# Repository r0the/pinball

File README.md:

# Ausgabemodule für Flipperautomaten

Für das Fakultativfach *Technisches Konstruieren* am [Gymnasium Kirchenfeld](https://www.gymkirchenfeld.ch/), in welchem Schülerinnen und Schüler einen Flipperautomaten bauen, entwickle ich elektronische Anzeigemodule. Kern der Module bildet ein
[Arduino](https://www.arduino.cc/)-Mikrocontroller-Board.

## Funktionalität

Die Module bieten die folgende Funktionalität:

- Zählen der Punkte
- Anzeige des aktuellen Punktestands
- Abspielen von Audiodateien
- Speichern des Punktehöchststands (Highscore)
- Steuerung von Lampen oder Leuchtdioden des Automaten
- Anzeige eines Lauftextes (nur Modul B)

## Varianten

Es gibt zwei Varianten, welche sich in der Art des Displays unterscheiden.

- Das **Variante A** verwendet zur Anzeige des Punktestands fünf LED-Segmentanzeigen.
- Das **Variante B** stellt Punktestand und allenfalls weitere Informationen auf einer oder mehreren
  LED-Matrixanzeigen dar.

Zur Zeit steht pro Jahrgang steht nur eine Variante zu Verfügung.

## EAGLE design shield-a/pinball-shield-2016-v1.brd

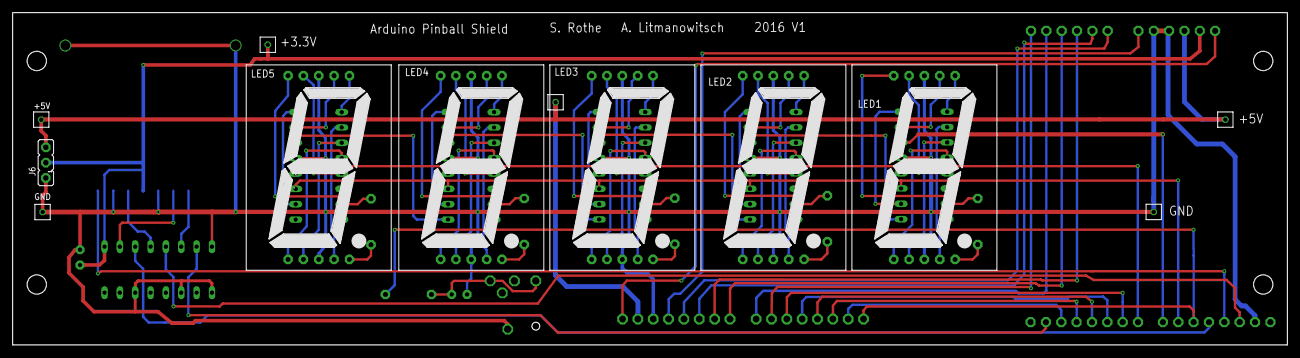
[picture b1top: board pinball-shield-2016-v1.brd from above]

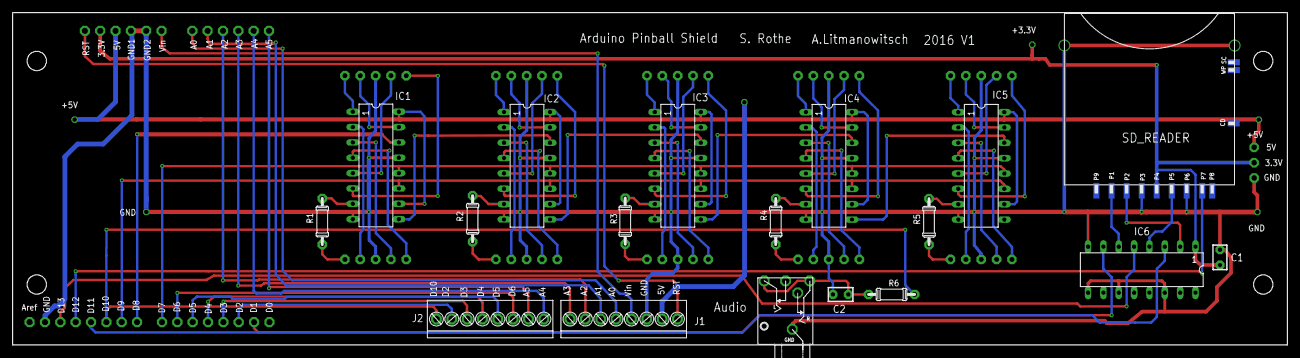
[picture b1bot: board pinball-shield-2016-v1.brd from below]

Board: 2 copper layers, 211.0 x 55.0 mm, 58 parts (18 on the bottom side), 77 nets.

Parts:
C1: 0.1uF; 02P101QK
C2: 1nF; 02P101QK
E$1: JACK_CONRAD_730294
E$2, E$3, E$4, E$5, E$8, E$9, E$10, E$12, E$13, E$14, E$15, E$16, E$17, E$18, E$19, E$20, E$21, E$22, E$23, E$24, E$25, E$26, E$27, E$28, E$29, E$30, E$31, E$32: DRILL040
E$6, E$7, E$11, E$33, E$34, E$35: CON01_FOR_AT2560_ALIT
IC1, IC2, IC3, IC4, IC5: SN74LV595; DIL16
IC6: 74LS4050; DIL16
J1, J2: PH2_54X8
J6: JP2
LED1, LED2, LED3, LED4, LED5: SC10-21; 7SEG-2.54
R1, R2, R3, R4, R5: 0204/7
R6: 470; 0204/7
SD_READER: 104H-TDA0-R

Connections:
3.3V: C1.2, E$14.P$1, E$35.1, IC6.1, J6.2, SD_READER.P4
+5V: E$7.1, E$11.1, E$15.P$1, E$34.1, IC1.10, IC1.16, IC2.10, IC2.16, IC3.10, IC3.16, IC4.10, IC4.16, IC5.10, IC5.16, J1.7, J6.3
GND: C1.1, C2.2, E$1.1, E$3.P$1, E$6.1, E$16.P$1, E$17.P$1, E$33.1, IC1.8, IC1.13, IC2.8, IC2.13, IC3.8, IC3.13, IC4.8, IC4.13, IC5.8, IC5.13, IC6.8, IC6.9, IC6.11, IC6.14, J1.6, J6.1, LED1.3, LED1.8, LED2.3, LED2.8, LED3.3, LED3.8, LED4.3, LED4.8, LED5.3, LED5.8, SD_READER.GND0, SD_READER.GND1, SD_READER.P3, SD_READER.P6
unnamed: IC4.15, LED4.7
unnamed: IC4.1, LED4.6
unnamed: IC4.2, LED4.4
unnamed: IC4.3, LED4.2
unnamed: IC4.4, LED4.1
unnamed: IC4.5, LED4.9
unnamed: IC4.6, LED4.10
unnamed: IC4.7, R4.2
unnamed: LED4.5, R4.1
unnamed: IC3.15, LED3.7
unnamed: IC3.1, LED3.6
unnamed: IC3.2, LED3.4
unnamed: IC3.3, LED3.2
unnamed: IC3.4, LED3.1
unnamed: IC3.5, LED3.9
unnamed: IC3.6, LED3.10
unnamed: IC3.7, R3.2
unnamed: LED3.5, R3.1
unnamed: IC2.15, LED2.7
unnamed: IC2.1, LED2.6
unnamed: IC2.2, LED2.4
unnamed: IC2.3, LED2.2
unnamed: IC2.4, LED2.1
unnamed: IC2.5, LED2.9
unnamed: IC2.6, LED2.10
unnamed: IC2.7, R2.2
unnamed: LED2.5, R2.1
unnamed: IC1.15, LED1.7
unnamed: IC1.1, LED1.6
unnamed: IC1.2, LED1.4
unnamed: IC1.3, LED1.2
unnamed: IC1.4, LED1.1
unnamed: IC1.5, LED1.9
unnamed: IC1.6, LED1.10
unnamed: IC1.7, R1.2
unnamed: LED1.5, R1.1
unnamed: IC5.15, LED5.7
unnamed: IC5.1, LED5.6
unnamed: IC5.2, LED5.4
unnamed: IC5.3, LED5.2
unnamed: IC5.4, LED5.1
unnamed: IC5.5, LED5.9
unnamed: IC5.6, LED5.10
unnamed: IC5.7, R5.2
unnamed: LED5.5, R5.1
S$1: E$10.P$1, IC1.11, IC2.11, IC3.11, IC4.11, IC5.11
S$2: E$25.P$1, IC1.12, IC2.12, IC3.12, IC4.12, IC5.12
S$3: E$12.P$1, IC1.14
S$4: IC1.9, IC2.14
S$5: IC2.9, IC3.14
S$6: IC3.9, IC4.14
S$7: IC4.9, IC5.14
S$8: E$13.P$1, J1.8
S$10: C2.1, E$1.2, E$1.5, R6.1
S$12: E$18.P$1, J1.5
S$13: E$19.P$1, J1.4
S$14: E$20.P$1, J1.3
S$15: E$21.P$1, J1.2
S$16: E$22.P$1, J1.1
S$17: E$29.P$1, J2.3
S$18: E$27.P$1, J2.5
S$19: E$26.P$1, J2.6
S$21: E$30.P$1, J2.2
S$22: E$24.P$1, J2.7
S$23: E$28.P$1, J2.4
S$24: E$23.P$1, J2.8
S$25: E$31.P$1, IC6.7
S$26: E$8.P$1, IC6.3
S$27: E$4.P$1, IC6.5
S$28: E$5.P$1, SD_READER.P7
S$29: IC6.6, SD_READER.P1
S$30: IC6.2, SD_READER.P2
S$31: IC6.4, SD_READER.P5
S$35: E$9.P$1, J2.1, R6.2

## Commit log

2015-12-22 Initial commit.
2015-12-22 Removed temporary files, added .gitignore.
2015-12-22 Fixed: Show demo text on reset.
2015-12-22 Moved Input class to own files, renamed to Pins.
2015-12-22 Updated TMRpcm library to v1.0
2015-12-22 Moved event names to program memory.
2015-12-22 Removed obsolete demo code.
2015-12-22 Renamed variables.
2015-12-23 Fixed: resetting number parameter when parsing multiple commands.
2015-12-23 2015: Scroll delay as define, doubled scroll speed.
2015-12-23 2015: Improvements in input handling
    - Event is active only once per activation of input.
    - Input delay as constant.
2015-12-24 Added customization hooks and custom code for some students.
2015-12-27 Added pinball shield 2016 schematics.
2016-01-11 Updated documentation.
2016-01-16 Added test for 2016 module.
2016-01-18 Added custom code for Noell.
2016-01-18 Fixed bug in command interpreter. 'b' and 'x' are now executed correctly.
2016-01-18 Fixed typo in README.md.
2016-01-27 Added init event 6 seconds after game over, fixed high score event.
2016-01-27 Improved custom code.
2016-02-09 Increased scroll speed.
2016-03-03 Factored out game logic into separate class.
2016-03-04 Moved SD access to separate class, cache SD card contents.
2016-03-16 2015 - Improved input signal detection: don't trigger on short peaks.
2016-03-16 2015 - Removed obsolete code.
2016-03-16 2015 - Fixed custom code (Noell).
2016-03-22 Started 2016 documentation.
2016-03-22 Update README.md
    Fixed image link.
2016-05-25 Added presentation.
2016-05-25 Work on presentation.
2016-05-26 Work on 2016 documentation.
2016-05-28 Enhanced documentation for 2016.
2016-06-04 Work on Module 2016.
2016-06-04 Added images
2016-06-09 Working audio output on pin 10.
2016-06-09 Added technical information.
2016-06-12 Work on documentation.
2016-06-16 Work on 2016 module.
2016-06-21 Added creation of PDFs from Markdown docs.
2016-06-21 Renamed schema files.
2016-08-20 Work on 2016 project.
2016-08-25 2016 Release 2
    - Changed variable names
    - Added countdown events
    - Fixed bugs
2016-10-23 Removed generated files.
2016-10-28 2016: Updated documentation
2016-11-01 Added highscore support: event, save, load
2016-11-04 Improved images in documentation.
2016-11-04 Fixed duplicate calling of events.
2017-01-14 Fixed large number problem.
2017-01-14 Added more display texts.
2017-01-14 Release version r4
2017-01-14 Now 1 maps correctly to HIGH output, 0 to LOW.
2017-01-14 Fixed docs.
2017-01-14 Fixed continue mask.
2017-01-14 Set output pins to LOW on start.
2017-01-14 Release r6
2017-01-15 README.md - Fixed layout
2017-01-25 Enhanced documentation: RGB LED stripe, programming of special mode
2017-01-25 Removed temporary files from repo.
2017-01-25 Added temporary pdf file pattern to .gitignore.
2017-01-25 Improved image of relay
2017-01-31 Added support for Nixie tube display.
